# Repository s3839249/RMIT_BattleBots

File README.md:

# RMIT_BattleBots

This Repository contains all the files that we will use for the design phase and the building phase of a battlebot.

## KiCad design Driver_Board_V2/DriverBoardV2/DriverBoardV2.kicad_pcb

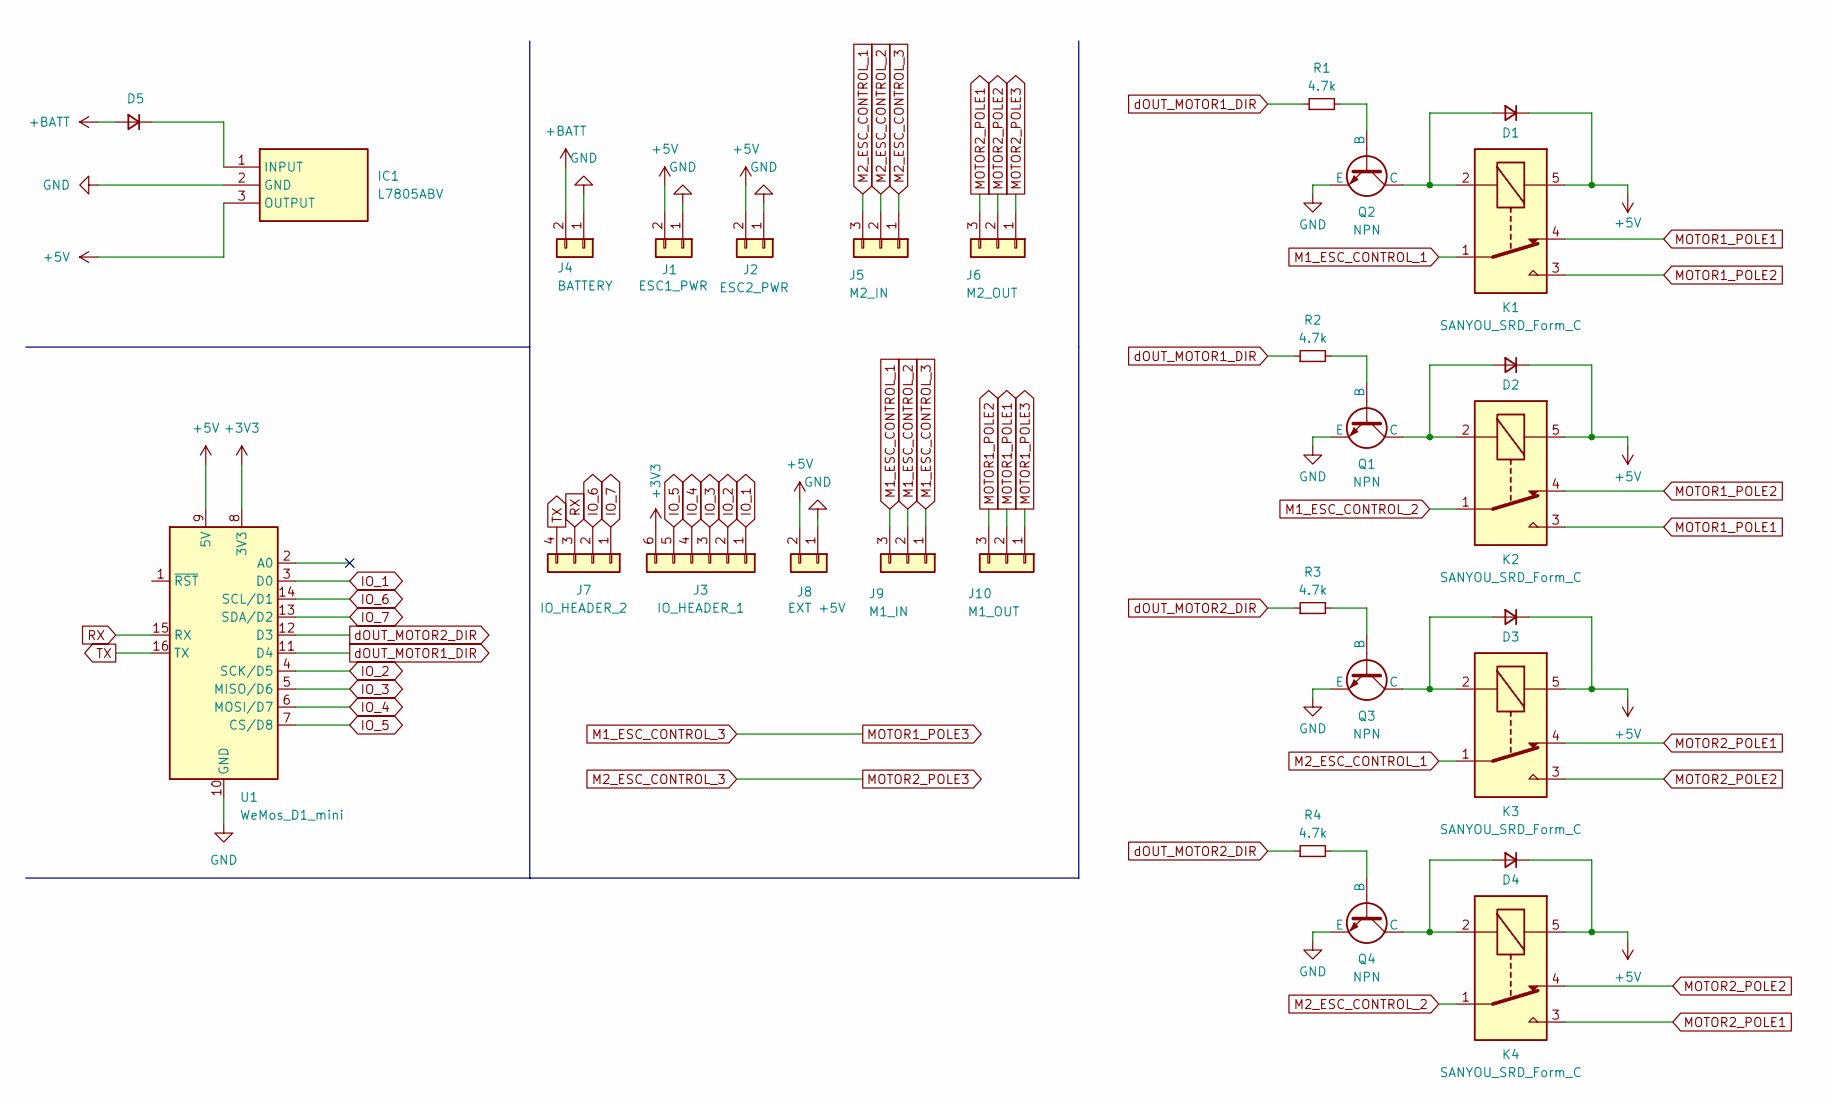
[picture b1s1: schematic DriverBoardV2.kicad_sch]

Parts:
D1, D2, D3, D4, D5: D_Small; D_DO-41_SOD81_P10.16mm_Horizontal
IC1: L7805ABV; TO-220-3_Horizontal_TabDown; Manufacturer_Part_Number L7805ABV; Mouser Part Number 511-L7805ABV
J1: ESC1_PWR; TerminalBlock_Xinya_XY308-2.54-2P_1x02_P2.54mm_Horizontal
J2: ESC2_PWR; TerminalBlock_Xinya_XY308-2.54-2P_1x02_P2.54mm_Horizontal
J3: IO_HEADER_1; PinHeader_1x06_P2.54mm_Vertical
J4: BATTERY; AMASS_XT60PW-M_1x02_P7.20mm_Horizontal
J5: M2_IN; TerminalBlock_Altech_AK300-3_P5.00mm
J6: M2_OUT; TerminalBlock_Altech_AK300-3_P5.00mm
J7: IO_HEADER_2; PinHeader_1x04_P2.54mm_Vertical
J8: EXT +5V; TerminalBlock_Xinya_XY308-2.54-2P_1x02_P2.54mm_Horizontal
J9: M1_IN; TerminalBlock_Altech_AK300-3_P5.00mm
J10: M1_OUT; TerminalBlock_Altech_AK300-3_P5.00mm
K1, K2, K3, K4: SANYOU_SRD_Form_C; Relay_SPDT_SANYOU_SRD_Series_Form_C
Q1, Q2, Q3, Q4: NPN; TO-92L_Inline
R1, R2, R3, R4: 4.7k; R_Axial_DIN0207_L6.3mm_D2.5mm_P15.24mm_Horizontal
U1: WeMos_D1_mini; WEMOS_D1_mini_light

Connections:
+3V3: J3.6, U1.8 (3V3)
+5V: D1.1 (K), D2.1 (K), D3.1 (K), D4.1 (K), IC1.3 (OUTPUT), J1.2, J2.2, J8.2, K1.5, K2.5, K3.5, K4.5, U1.9 (5V)
+BATT: D5.2 (A), J4.2
GND: IC1.2 (GND), J1.1, J2.1, J4.1, J8.1, Q1.3 (E), Q2.3 (E), Q3.3 (E), Q4.3 (E), U1.10 (GND)
IO_1: J3.1, U1.3 (D0)
IO_2: J3.2, U1.4 (SCK/D5)
IO_3: J3.3, U1.5 (MISO/D6)
IO_4: J3.4, U1.6 (MOSI/D7)
IO_5: J3.5, U1.7 (CS/D8)
IO_6: J7.2, U1.14 (SCL/D1)
IO_7: J7.1, U1.13 (SDA/D2)
M1_ESC_CONTROL_1: J9.3, K1.1
M1_ESC_CONTROL_2: J9.2, K2.1
M1_ESC_CONTROL_3: J9.1, J10.1
M2_ESC_CONTROL_1: J5.3, K3.1
M2_ESC_CONTROL_2: J5.2, K4.1
M2_ESC_CONTROL_3: J5.1, J6.1
MOTOR1_POLE1: J10.2, K1.4, K2.3
MOTOR1_POLE2: J10.3, K1.3, K2.4
MOTOR2_POLE1: J6.3, K3.4, K4.3
MOTOR2_POLE2: J6.2, K3.3, K4.4
unnamed: D1.2 (A), K1.2, Q2.1 (C)
unnamed: D2.2 (A), K2.2, Q1.1 (C)
unnamed: D3.2 (A), K3.2, Q3.1 (C)
unnamed: D4.2 (A), K4.2, Q4.1 (C)
unnamed: D5.1 (K), IC1.1 (INPUT)
unnamed: Q1.2 (B), R2.2
unnamed: Q2.2 (B), R1.2
unnamed: Q3.2 (B), R3.2
unnamed: Q4.2 (B), R4.2
RX: J7.3, U1.15 (RX)
TX: J7.4, U1.16 (TX)
dOUT_MOTOR1_DIR: R1.1, R2.1, U1.11 (D4)
dOUT_MOTOR2_DIR: R3.1, R4.1, U1.12 (D3)

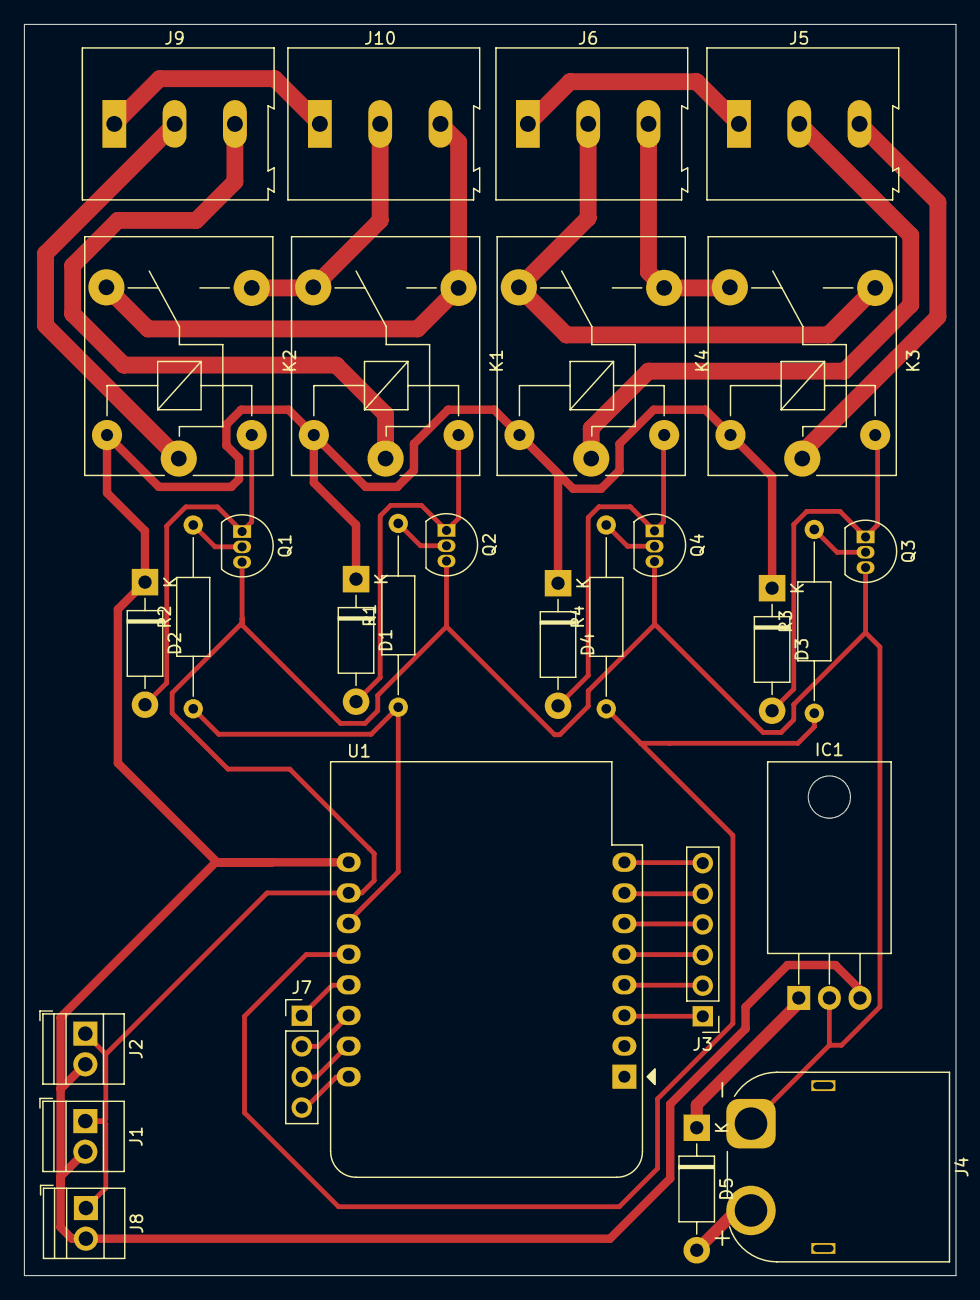
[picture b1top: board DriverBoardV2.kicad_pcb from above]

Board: 2 copper layers, 77.3 x 103.8 mm, 29 parts (0 on the bottom side), 34 nets.

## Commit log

2024-08-23 Add initial README and CONTRIBUTING (#1)
    * Add initial README and CONTRIBUTING
    * updating contribution to include the fork instruction
    ---------
2024-08-23 Initial schematic and layout for workaround fix for ESC direction control
2024-08-23 Adding in project specific symbol & footprint libraries
2024-08-23 Updating .gitignore to ignore gerbers and drill files for now, need to find a better workflow for these
2024-08-23 Updated schematic due to layout consideration and increase 5V rail track sizes
